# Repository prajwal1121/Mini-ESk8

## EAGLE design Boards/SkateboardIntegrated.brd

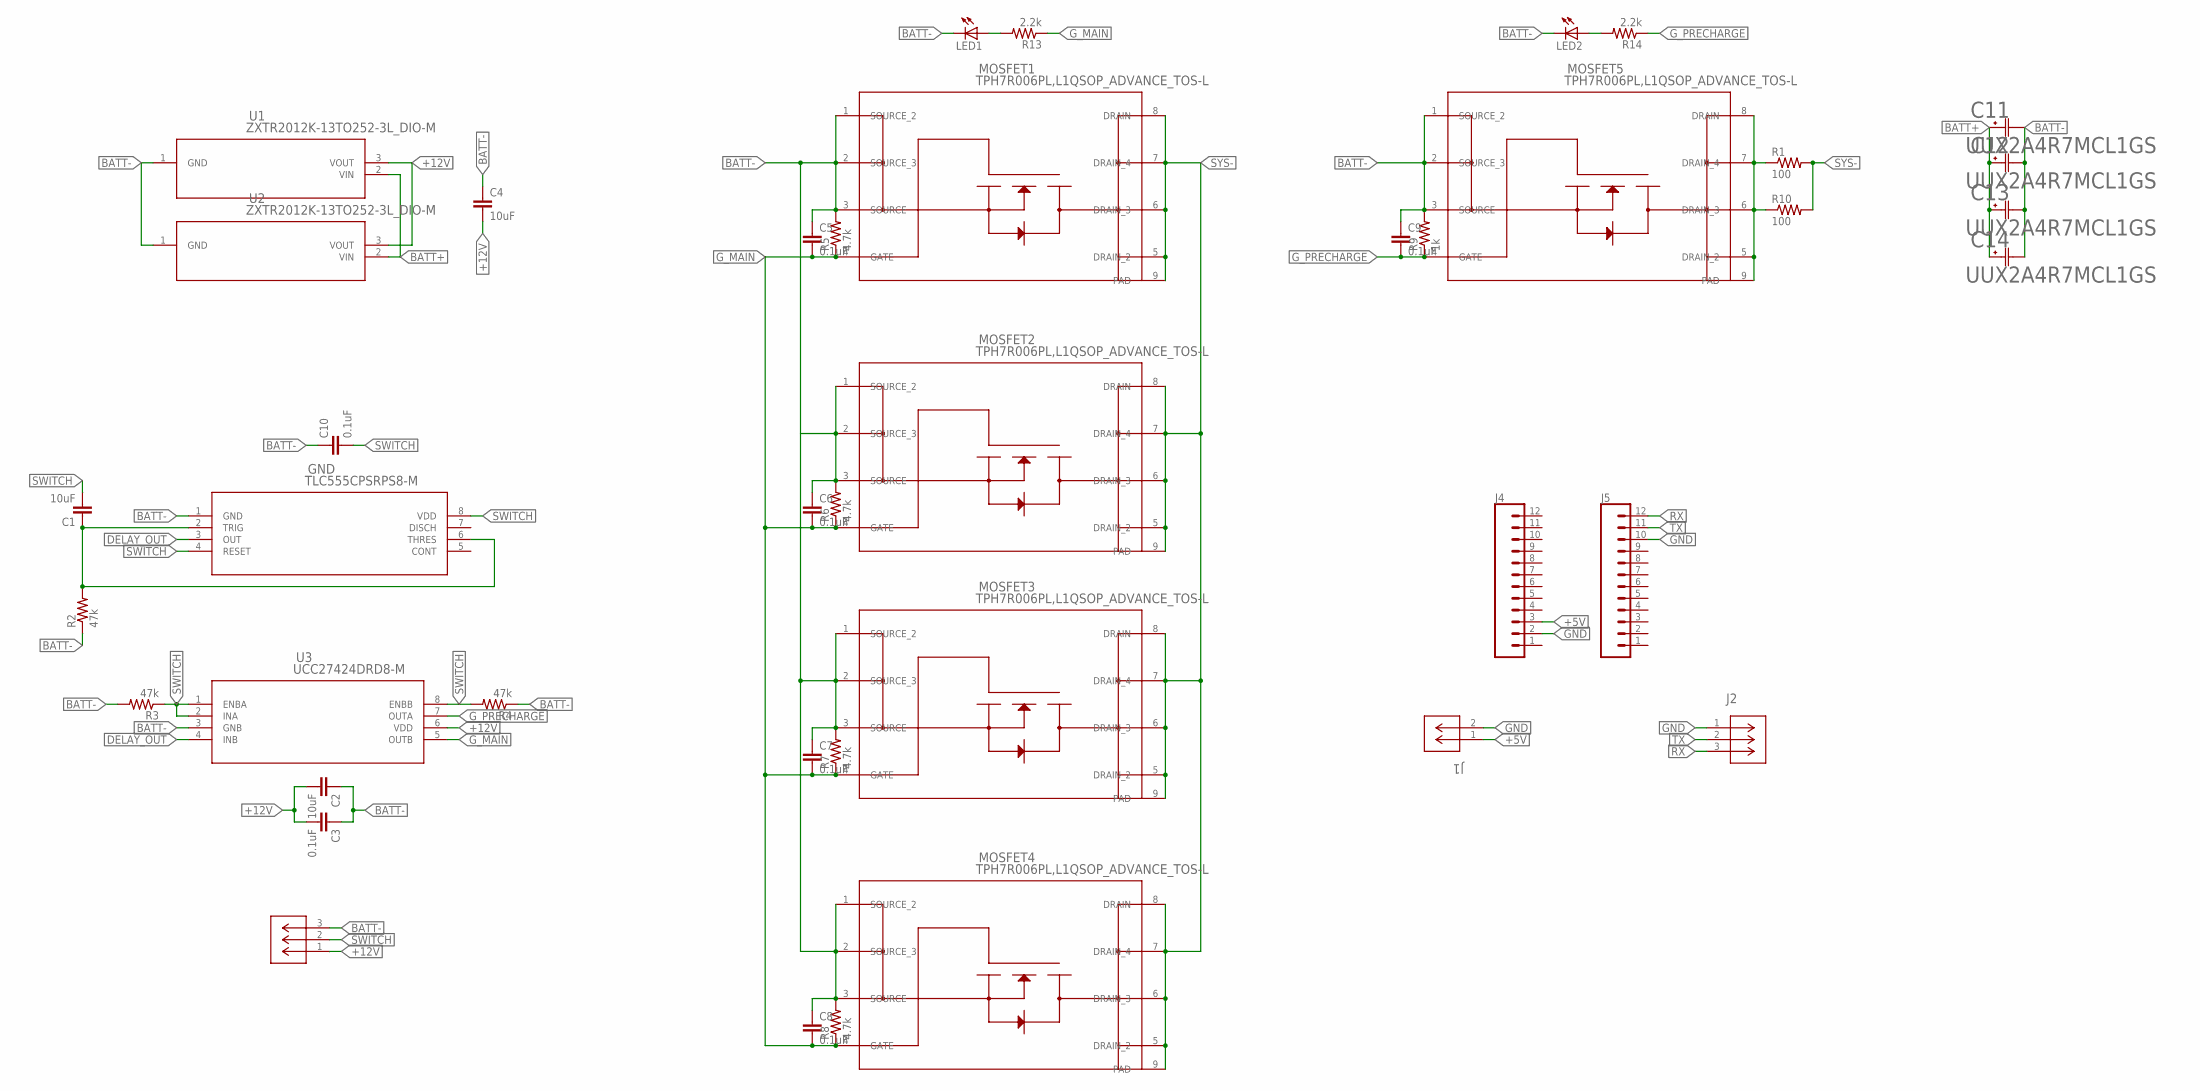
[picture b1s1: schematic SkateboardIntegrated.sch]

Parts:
C1, C2, C4: 10uF; 0805
C3, C5, C6, C7, C8, C9, C10: 0.1uF; 0805
C11, C12, C13, C14: UUX2A4R7MCL1GS; CAP_UCD_8X6P2_NCH
GND: TLC555CPSRPS8-M; PS8-M
J1: 1775470-2; CONN2_1775470-2_TEC
J2, J3: 1775470-3; CONN3_1775470-3_TEC
J4, J5: CONN_12SMD_ALT; 1X12_SMD_ALT
LED1, LED2: LEDCHIPLED_0805; CHIPLED_0805
MOSFET1, MOSFET2, MOSFET3, MOSFET4, MOSFET5: TPH7R006PL,L1QSOP_ADVANCE_TOS-L; SOP_ADVANCE_TOS-L
R1, R10: 100; R2512
R2, R3, R4: 47k; R0805
R5, R6, R7, R8: 4.7k; R0805
R9: 1k; R0805
R13, R14: 2.2k; R0805
U1, U2: ZXTR2012K-13TO252-3L_DIO-M; TO252-3L_DIO-M
U3: UCC27424DRD8-M; D8-M

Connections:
+5V: J1.1, J4.3
+12V: C2.2, C3.2, C4.2, J3.1, U1.3 (VOUT), U2.3 (VOUT), U3.6 (VDD)
BATT+: C11.1, C12.1, C13.1, C14.1, U1.2 (VIN), U2.2 (VIN)
BATT-: C2.1, C3.1, C4.1, C5.1, C6.1, C7.1, C8.1, C9.1, C10.1, C11.2, C12.2, C13.2, C14.2, GND.1 (GND), J3.3, LED1.C, LED2.C, MOSFET1.1 (SOURCE_2), MOSFET1.2 (SOURCE_3), MOSFET1.3 (SOURCE), MOSFET2.1 (SOURCE_2), MOSFET2.2 (SOURCE_3), MOSFET2.3 (SOURCE), MOSFET3.1 (SOURCE_2), MOSFET3.2 (SOURCE_3), MOSFET3.3 (SOURCE), MOSFET4.1 (SOURCE_2), MOSFET4.2 (SOURCE_3), MOSFET4.3 (SOURCE), MOSFET5.1 (SOURCE_2), MOSFET5.2 (SOURCE_3), MOSFET5.3 (SOURCE), R2.1, R3.2, R4.1, R5.2, R6.2, R7.2, R8.2, R9.2, U1.1 (GND), U2.1 (GND), U3.3 (GNB)
DELAY_OUT: GND.3 (OUT), U3.4 (INB)
GND: J1.2, J2.1, J4.2, J5.10
G_MAIN: C5.2, C6.2, C7.2, C8.2, MOSFET1.4 (GATE), MOSFET2.4 (GATE), MOSFET3.4 (GATE), MOSFET4.4 (GATE), R5.1, R6.1, R7.1, R8.1, R13.1, U3.5 (OUTB)
G_PRECHARGE: C9.2, MOSFET5.4 (GATE), R9.1, R14.1, U3.7 (OUTA)
unnamed: C1.1, GND.2 (TRIG), GND.6 (THRES), R2.2
unnamed: MOSFET5.5 (DRAIN_2), MOSFET5.6 (DRAIN_3), MOSFET5.7 (DRAIN_4), MOSFET5.8 (DRAIN), MOSFET5.9 (PAD), R1.1, R10.1
unnamed: LED1.A, R13.2
unnamed: LED2.A, R14.2
RX: J2.3, J5.12
SWITCH: C1.2, C10.2, GND.4 (RESET), GND.8 (VDD), J3.2, R3.1, R4.2, U3.1 (ENBA), U3.2 (INA), U3.8 (ENBB)
SYS-: MOSFET1.5 (DRAIN_2), MOSFET1.6 (DRAIN_3), MOSFET1.7 (DRAIN_4), MOSFET1.8 (DRAIN), MOSFET1.9 (PAD), MOSFET2.5 (DRAIN_2), MOSFET2.6 (DRAIN_3), MOSFET2.7 (DRAIN_4), MOSFET2.8 (DRAIN), MOSFET2.9 (PAD), MOSFET3.5 (DRAIN_2), MOSFET3.6 (DRAIN_3), MOSFET3.7 (DRAIN_4), MOSFET3.8 (DRAIN), MOSFET3.9 (PAD), MOSFET4.5 (DRAIN_2), MOSFET4.6 (DRAIN_3), MOSFET4.7 (DRAIN_4), MOSFET4.8 (DRAIN), MOSFET4.9 (PAD), R1.2, R10.2
TX: J2.2, J5.11

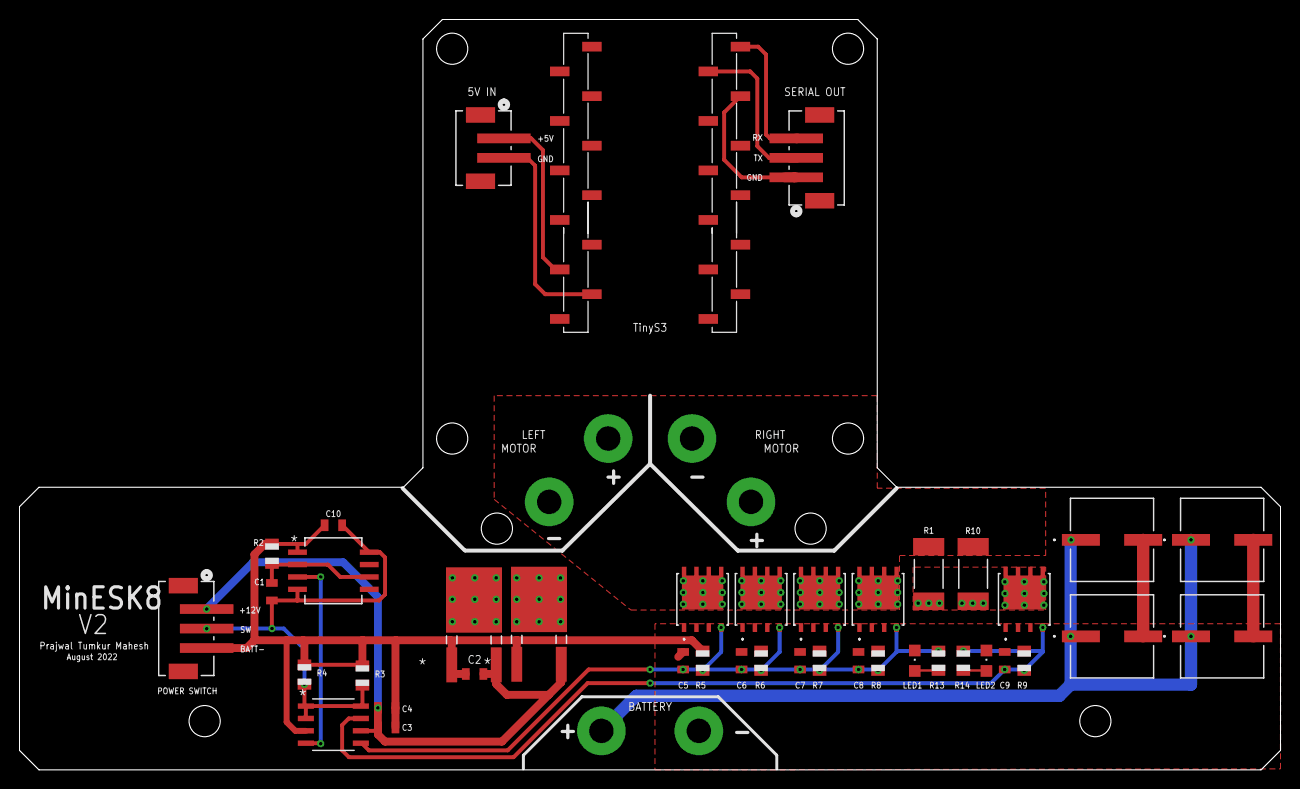
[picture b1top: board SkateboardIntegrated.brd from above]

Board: 2 copper layers, 129.4 x 77.0 mm, 42 parts (0 on the bottom side), 16 nets.

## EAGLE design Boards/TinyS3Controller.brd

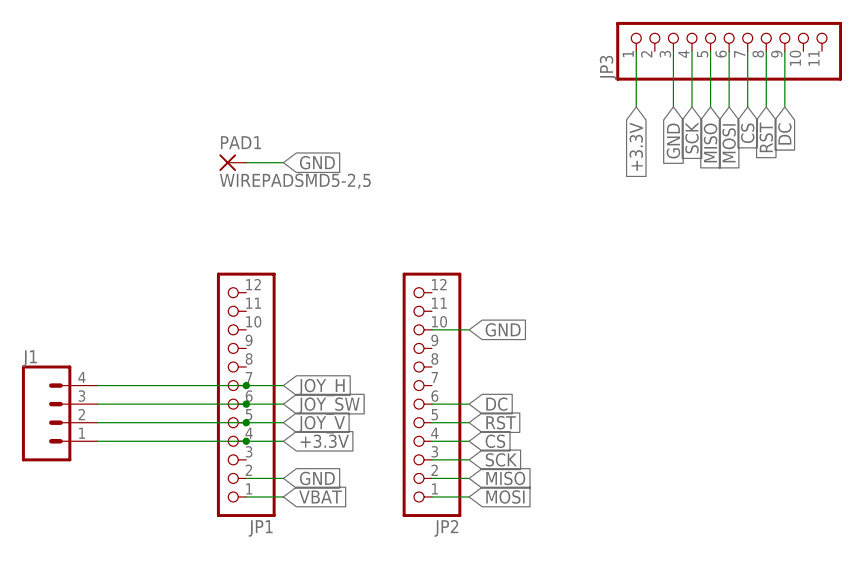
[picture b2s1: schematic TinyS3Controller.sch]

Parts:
J1: CONN_04PTH; 1X04
JP1, JP2: PINHD-1X12-CB; 1X12-CB
JP3: PINHD-1X11; 1X11
PAD1: WIREPADSMD5-2,5; 5-2,5

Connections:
+3.3V: J1.1, JP1.4, JP3.1
CS: JP2.4, JP3.7
DC: JP2.6, JP3.9
GND: JP1.2, JP2.10, JP3.3, PAD1.1
JOY_H: J1.4, JP1.7
JOY_SW: J1.3, JP1.6
JOY_V: J1.2, JP1.5
MISO: JP2.2, JP3.5
MOSI: JP2.1, JP3.6
RST: JP2.5, JP3.8
SCK: JP2.3, JP3.4
VBAT: JP1.1

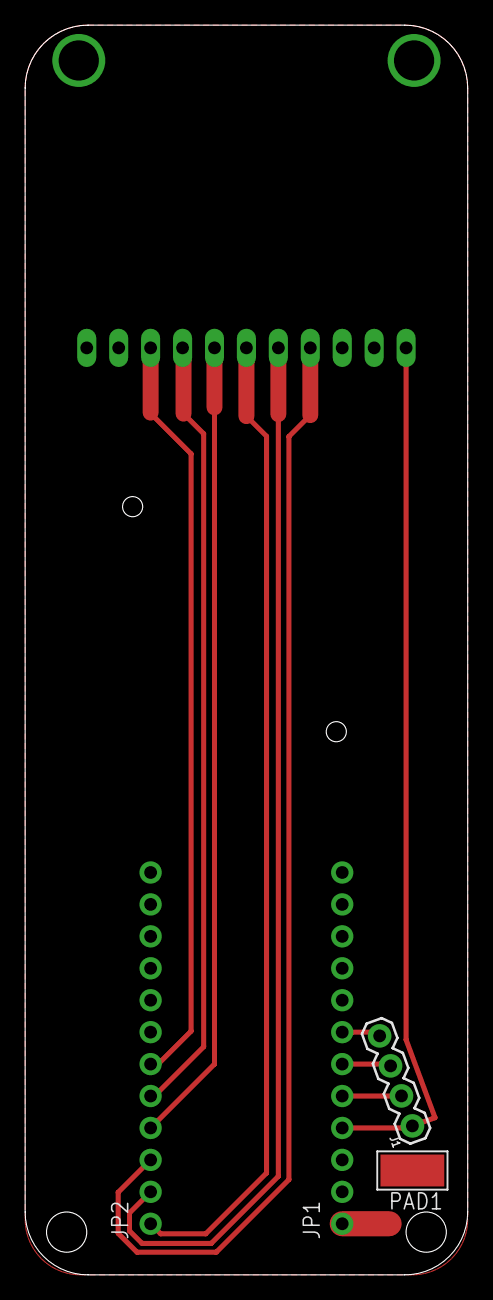
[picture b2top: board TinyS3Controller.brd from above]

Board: 2 copper layers, 35.2 x 99.4 mm, 5 parts (1 on the bottom side), 11 nets.

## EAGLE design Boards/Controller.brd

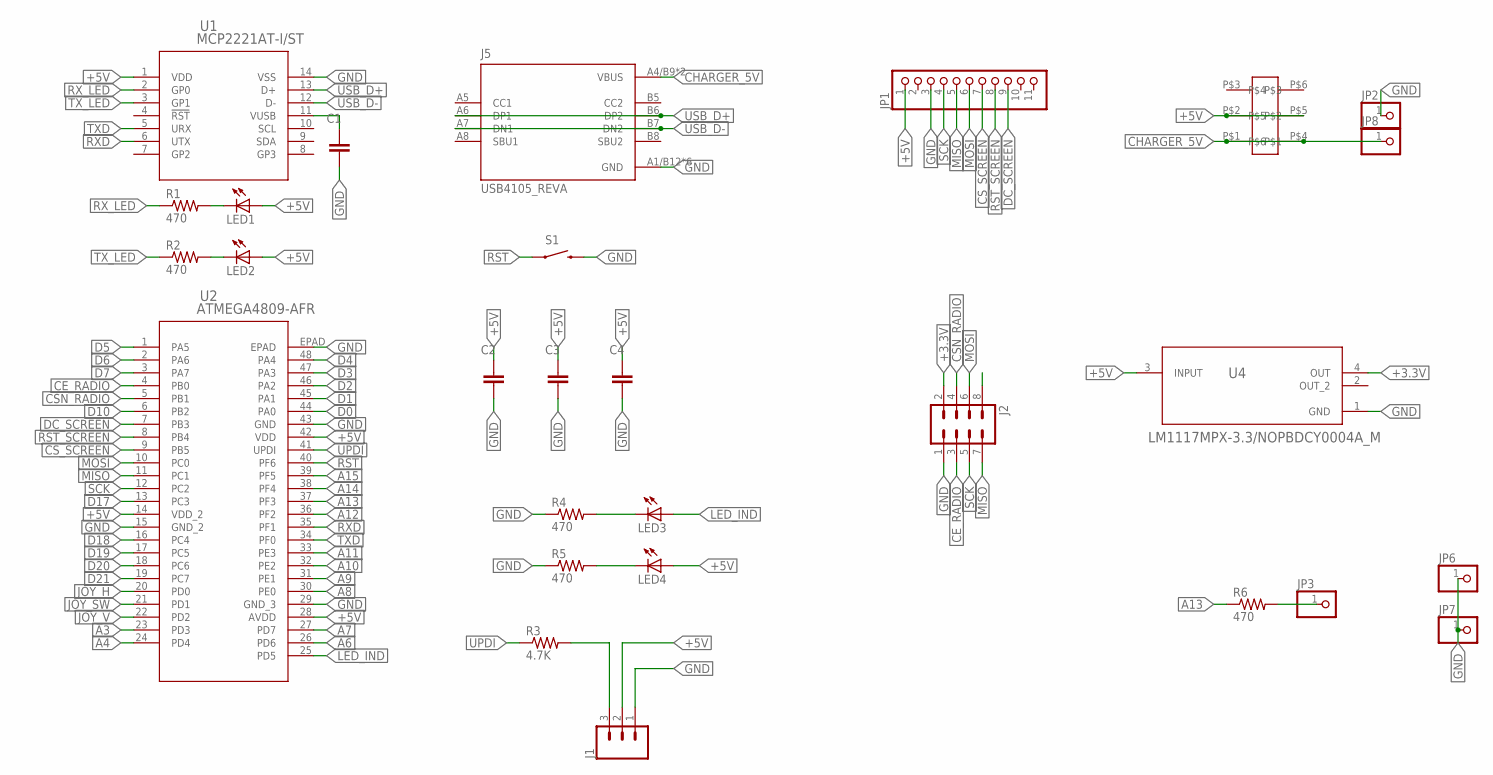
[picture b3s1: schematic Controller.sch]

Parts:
C1: 0.22uF; CAP_0805
C2, C3, C4: 0.1uF; CAP_0805
J1: CONN_03SMD_RA_MALE; 1X03_SMD_RA_MALE
J2: MA04-2
J5: USB4105_REVA; GCT_USB4105_REVA
JP1: PINHD-1X11; 1X11
JP2, JP3, JP6, JP7, JP8: PINHD-1X1; 1X01
LED1, LED2, LED3, LED4: LEDCHIPLED_0805; CHIPLED_0805
R1, R2, R4, R5, R6: 470; R0805
R3: 4.7K; R0805
S1: RS032G05A3SM-SPST-MOMENTARY-SWSMD-1101NE; TACTILE-SWITCH-1101NE
U1: MCP2221AT-I/ST; TSSOP14_ST_MCH
U2: ATMEGA4809-AFR; TQFP48_7X7MC_MCH
U4: LM1117MPX-3.3/NOPBDCY0004A_M; DCY0004A_M
U$47: JS202011JAQN

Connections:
+3.3V: J2.2, U4.4 (OUT)
+5V: C2.1, C3.1, C4.1, J1.2, JP1.1, LED1.A, LED2.A, LED4.A, U1.1 (VDD), U2.14 (VDD_2), U2.28 (AVDD), U2.42 (VDD), U4.3 (INPUT), U$47.P$2, U$47.P$5
A3: U2.23 (PD3)
A4: U2.24 (PD4)
A6: U2.26 (PD6)
A7: U2.27 (PD7)
A8: U2.30 (PE0)
A9: U2.31 (PE1)
A10: U2.32 (PE2)
A11: U2.33 (PE3)
A12: U2.36 (PF2)
A13: R6.1, U2.37 (PF3)
A14: U2.38 (PF4)
A15: U2.39 (PF5)
CE_RADIO: J2.3, U2.4 (PB0)
CHARGER_5V: J5.A4/B9 (VBUS), J5.B4/A9 (VBUS), JP8.1, U$47.P$1, U$47.P$4
CSN_RADIO: J2.4, U2.5 (PB1)
CS_SCREEN: JP1.7, U2.9 (PB5)
D0: U2.44 (PA0)
D1: U2.45 (PA1)
D2: U2.46 (PA2)
D3: U2.47 (PA3)
D4: U2.48 (PA4)
D5: U2.1 (PA5)
D6: U2.2 (PA6)
D7: U2.3 (PA7)
D10: U2.6 (PB2)
D17: U2.13 (PC3)
D18: U2.16 (PC4)
D19: U2.17 (PC5)
D20: U2.18 (PC6)
D21: U2.19 (PC7)
DC_SCREEN: JP1.9, U2.7 (PB3)
GND: C1.2, C2.2, C3.2, C4.2, J1.1, J2.1, J5.A1/B12 (GND), J5.B1/A12 (GND), J5.G1 (GND), J5.G2 (GND), J5.G3 (GND), J5.G4 (GND), JP1.3, JP2.1, JP6.1, JP7.1, R4.1, R5.1, S1.2, U1.14 (VSS), U2.15 (GND_2), U2.29 (GND_3), U2.43 (GND), U2.EPAD, U4.1 (GND)
JOY_H: U2.20 (PD0)
JOY_SW: U2.21 (PD1)
JOY_V: U2.22 (PD2)
LED_IND: LED3.A, U2.25 (PD5)
MISO: J2.7, JP1.5, U2.11 (PC1)
MOSI: J2.6, JP1.6, U2.10 (PC0)
unnamed: LED1.C, R1.2
unnamed: LED2.C, R2.2
unnamed: C1.1, U1.11 (VUSB)
unnamed: JP3.1, R6.2
unnamed: LED3.C, R4.2
unnamed: LED4.C, R5.2
unnamed: J1.3, R3.2
OUT_2: U4.2 (OUT_2)
RST: S1.1, U2.40 (PF6)
RST_SCREEN: JP1.8, U2.8 (PB4)
RXD: U1.6 (UTX), U2.35 (PF1)
RX_LED: R1.1, U1.2 (GP0)
SCK: J2.5, JP1.4, U2.12 (PC2)
TXD: U1.5 (URX), U2.34 (PF0)
TX_LED: R2.1, U1.3 (GP1)
UPDI: R3.1, U2.41 (UPDI)
USB_D+: J5.A6 (DP1), J5.B6 (DP2), U1.13 (D+)
USB_D-: J5.A7 (DN1), J5.B7 (DN2), U1.12 (D-)

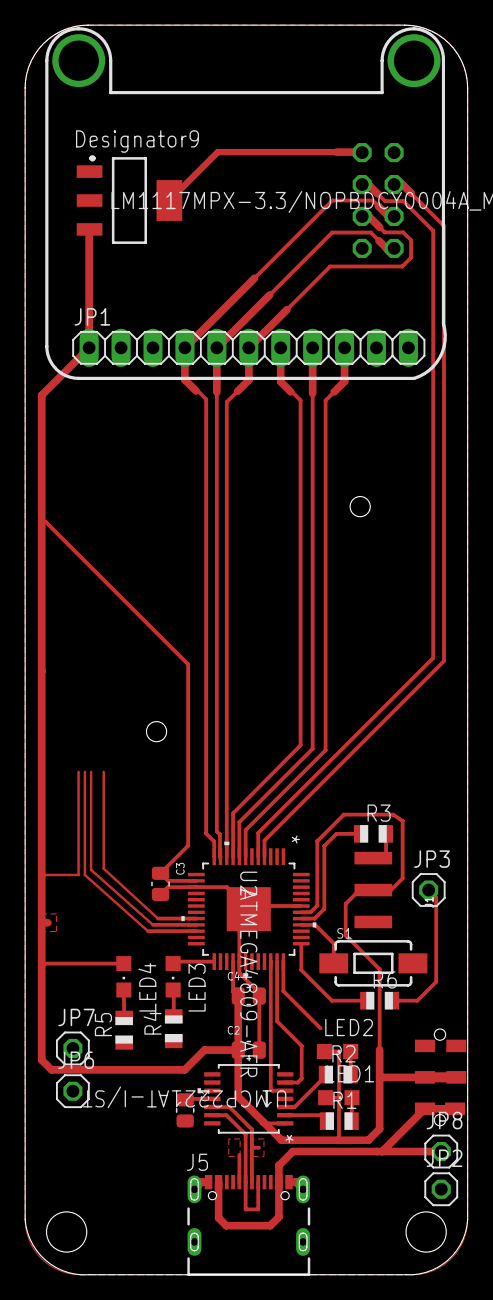
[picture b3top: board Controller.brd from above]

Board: 2 copper layers, 35.2 x 99.4 mm, 28 parts (1 on the bottom side), 29 nets.

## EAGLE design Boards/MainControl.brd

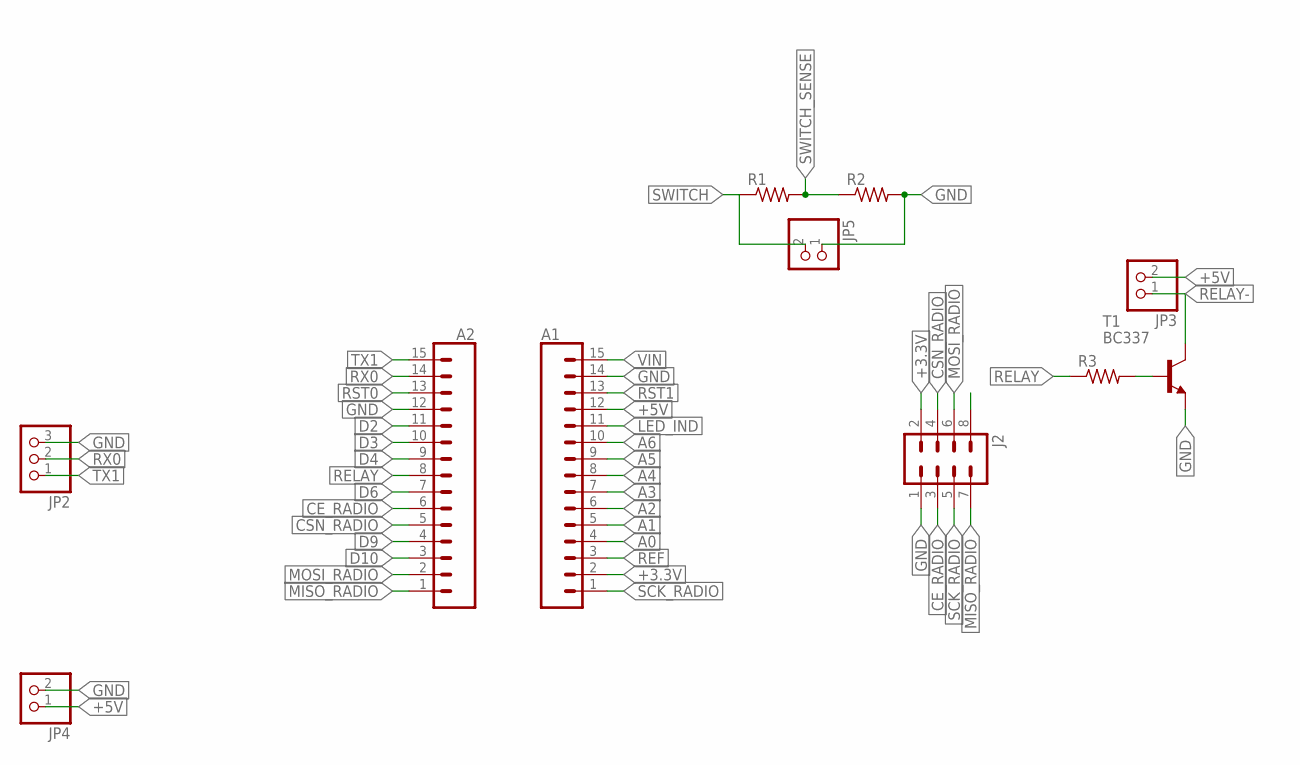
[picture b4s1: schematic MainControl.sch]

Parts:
A1, A2: CONN_15; 1X15
J2: MA04-2
JP2: PINHD-1X3; 1X03
JP3, JP4, JP5: PINHD-1X2; 1X02
R1, R2, R3: R-US_0204/7; 0204/7
T1: BC337; TO92

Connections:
+3.3V: A1.2, J2.2
+5V: A1.12, JP3.2, JP4.1
A0: A1.4
A1: A1.5
A2: A1.6
A3: A1.7
A4: A1.8
A5: A1.9
A6: A1.10
CE_RADIO: A2.6, J2.3
CSN_RADIO: A2.5, J2.4
D2: A2.11
D3: A2.10
D4: A2.9
D6: A2.7
D9: A2.4
D10: A2.3
GND: A1.14, A2.12, J2.1, JP2.3, JP4.2, JP5.1, R2.2, T1.1 (E)
LED_IND: A1.11
MISO_RADIO: A2.1, J2.7
MOSI_RADIO: A2.2, J2.6
unnamed: R3.2, T1.2 (B)
REF: A1.3
RELAY: A2.8, R3.1
RELAY-: JP3.1, T1.3 (C)
RST0: A2.13
RST1: A1.13
RX0: A2.14, JP2.2
SCK_RADIO: A1.1, J2.5
SWITCH: JP5.2, R1.1
SWITCH_SENSE: R1.2, R2.1
TX1: A2.15, JP2.1
VIN: A1.15

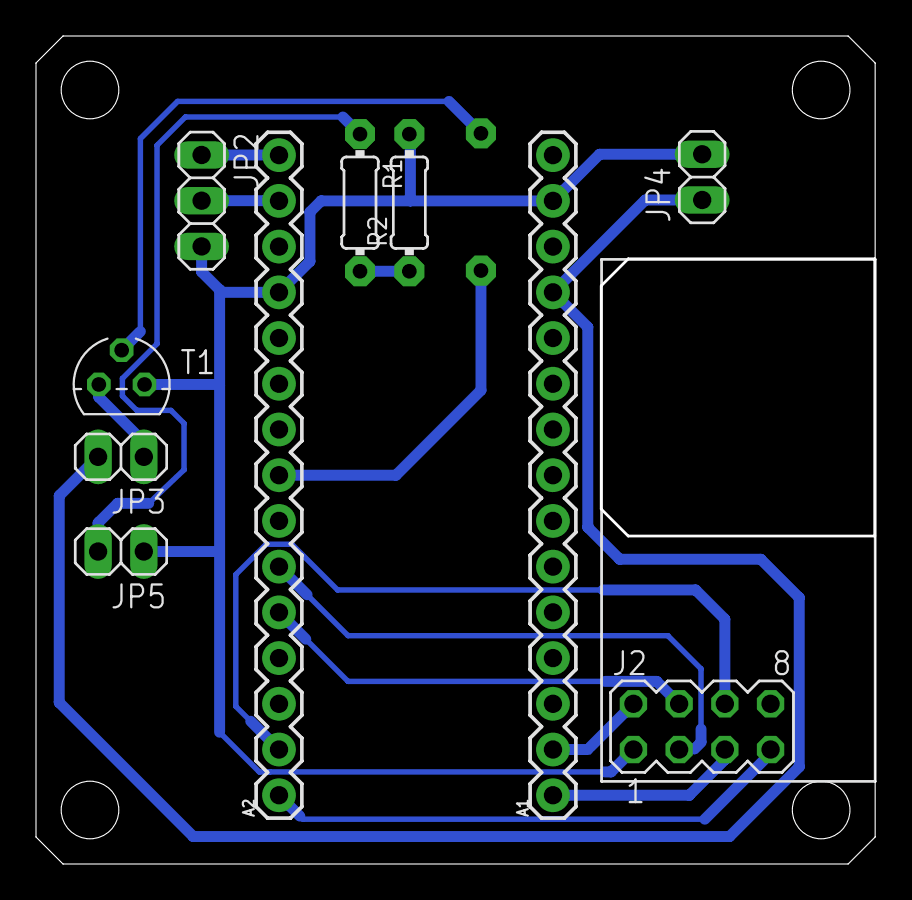
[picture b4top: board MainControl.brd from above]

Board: 2 copper layers, 46.5 x 45.8 mm, 11 parts (1 on the bottom side), 15 nets.

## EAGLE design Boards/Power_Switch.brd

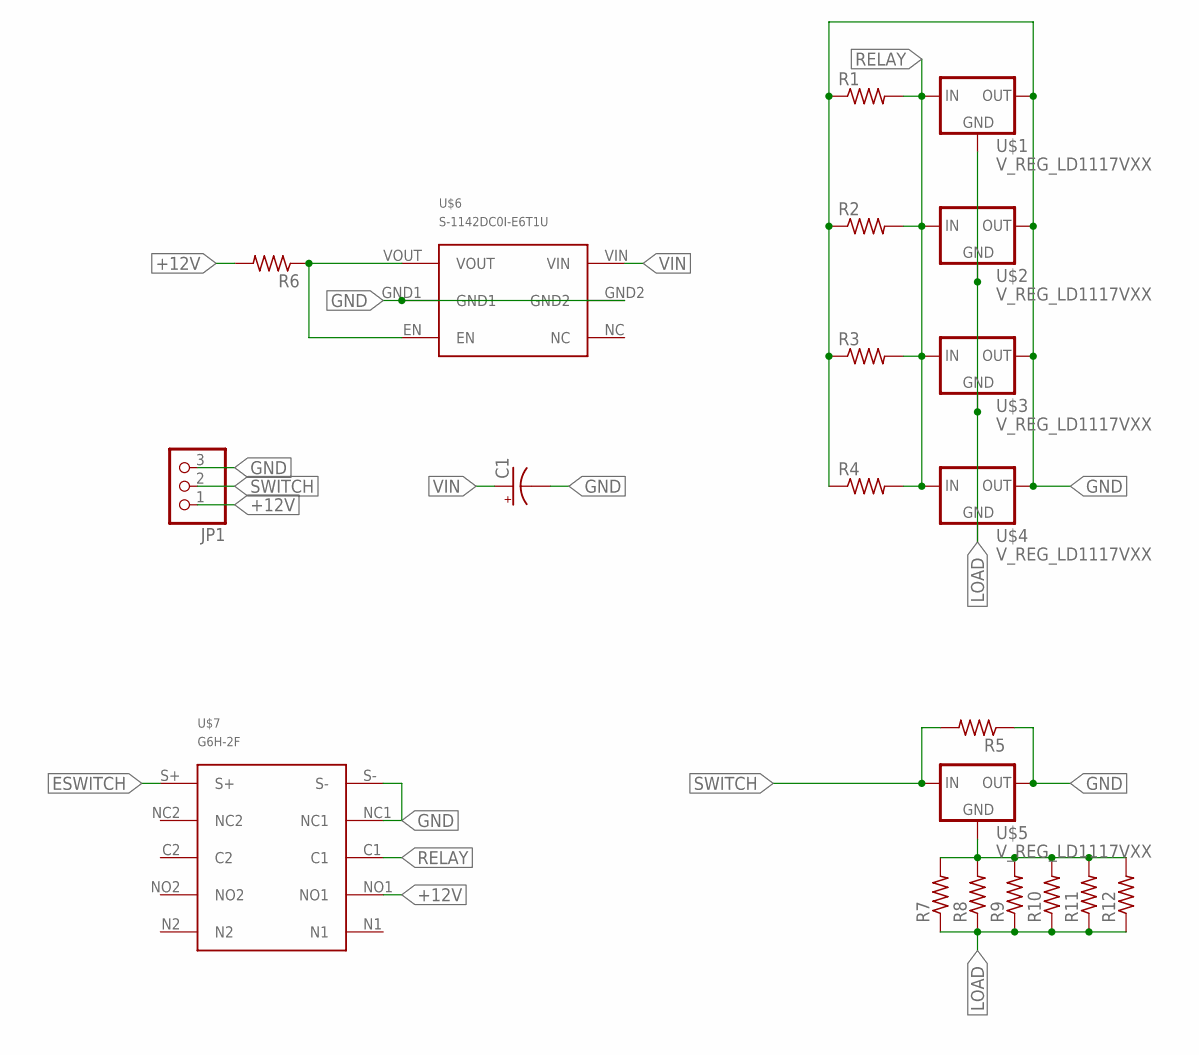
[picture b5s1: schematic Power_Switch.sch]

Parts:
C1: CPOL-US153CLV-0810; 153CLV-0810
JP1: PINHD-1X3; 1X03
R1, R2, R3, R4, R5, R6, R7, R8, R9, R10, R11, R12: R-US_R0805; R0805
U$1, U$2, U$3, U$4, U$5: V_REG_LD1117VXX; 78XXL
U$6: S-1142DC0I-E6T1U
U$7: G6H-2F

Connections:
+12V: JP1.1, R6.2, U$7.NO1
ESWITCH: U$7.S+
GND: C1.-, JP1.3, R1.1, R2.1, R3.1, R4.1, R5.1, U$1.OUT, U$2.OUT, U$3.OUT, U$4.OUT, U$5.OUT, U$6.GND1, U$6.GND2, U$7.NC1, U$7.S-
LOAD: R7.1, R8.1, R9.1, R10.1, R11.1, R12.1, U$1.GND, U$2.GND, U$3.GND, U$4.GND
unnamed: R6.1, U$6.EN, U$6.VOUT
unnamed: R7.2, R8.2, R9.2, R10.2, R11.2, R12.2, U$5.GND
RELAY: R1.2, R2.2, R3.2, R4.2, U$1.IN, U$2.IN, U$3.IN, U$4.IN, U$7.C1
SWITCH: JP1.2, R5.2, U$5.IN
VIN: C1.+, U$6.VIN

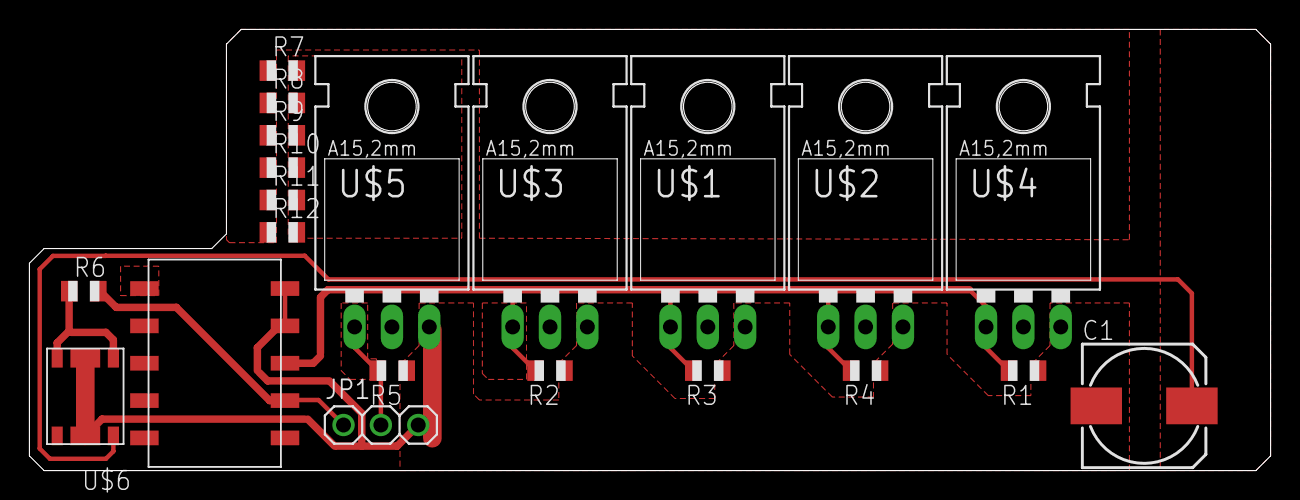
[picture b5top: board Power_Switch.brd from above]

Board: 2 copper layers, 84.4 x 30.0 mm, 21 parts (0 on the bottom side), 8 nets.

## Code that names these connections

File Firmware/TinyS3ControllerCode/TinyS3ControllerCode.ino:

#include <UMS3.h>
UMS3 ums3;

#include <esp_now.h>
#include <WiFi.h>

//#define USE_ASYNC_UPDATES

#include <Adafruit_GFX.h>
#include <Adafruit_ST7789.h> // Hardware-specific library for ST7789
#include <SPI.h>

//SCREEN PINS
#define SCREEN_CS   34
#define SCREEN_RST  9 
#define SCREEN_DC   8
//Create TFT object with correct pins
Adafruit_ST7789 tft = Adafruit_ST7789(SCREEN_CS, SCREEN_DC, SCREEN_RST);

uint16_t boxColor = 0x76D8;
uint16_t axisColor = 0x2207;

//JOYSTICK PINS
#define JOY_V  A0
#define JOY_H  A2 
#define JOY_SW A1
int joystick_x = 128;
int joystick_y = 128;
bool joystick_sw = 0;
int lastPosX = 0;
int lastPosY = 0;

//BATTERY PINS
float remoteBatteryVoltage = 0.0;
float lastRemoteBatteryVoltage = 0.0;
float remoteBatteryVoltageOffset = 0.0;

//BOARD BATTERY
byte boardBatteryCells = 10;
float boardBatteryVoltage = 0.0;
float lastBoardBatteryVoltage = 0.0;
float boardBatteryVoltageOffset = 0.0;

//BOARD ODOMETRY
int8_t mph = 0;
int8_t lastMph = 0;
int totalMiles = 69;
int tripMiles = 240;
const float rpmScaling = ((((90.0/25.4)/12.0)/5280.0)*3.14)*60.0;
const float motorPolePairs = 10.0;

//RADIO SETUP
//A: F4:12:FA:4F:A5:B0
uint8_t broadcastAddress[] = {0xF4, 0x12, 0xFA, 0x4F, 0xA5, 0xB0};

//Struct for holding board telemetry
typedef struct TelemetryStruct {
  float voltage;
  long rpm;
  long tach_abs;
} TelemetryStruct;

TelemetryStruct telemetry;
esp_now_peer_info_t peerInfo;

// Callback when data is sent
void OnDataSent(const uint8_t *mac_addr, esp_now_send_status_t status) {
//  Serial.print("\r\nLast Packet Send Status:\t");
//  Serial.println(status == ESP_NOW_SEND_SUCCESS ? "Delivery Success" : "Delivery Fail");
//  if (status ==0){
//    success = "Delivery Success :)";
//  }
//  else{
//    success = "Delivery Fail :(";
//  }
}

// Callback when data is received
void OnDataRecv(const uint8_t * mac, const uint8_t *incomingData, int len) {
  memcpy(&telemetry, incomingData, sizeof(telemetry));
  boardBatteryVoltage = telemetry.voltage;
  mph = telemetry.rpm/motorPolePairs*rpmScaling;
  tripMiles = telemetry.tach_abs;
}

void boardBatteryDisplay(){
  if (abs(boardBatteryVoltage-lastBoardBatteryVoltage)>0.1){
    tft.fillRoundRect(1, 0, tft.width()-2, 4, 2, ST77XX_BLACK);
    tft.drawRoundRect(1, 0, tft.width()-2, 4, 2, ST77XX_GREEN);
    
    int fillamount = boardBatteryVoltage/(4.2*boardBatteryCells)*(tft.width()-2);
    uint16_t color = 0;
    if (boardBatteryVoltage > (3.8*boardBatteryCells) and boardBatteryVoltage <= (4.2*boardBatteryCells)){
      color = ST77XX_GREEN;
    }
    else if (boardBatteryVoltage > (3.4*boardBatteryCells) and boardBatteryVoltage <= (3.8*boardBatteryCells)){
      color = ST77XX_YELLOW;
    }
    else if (boardBatteryVoltage <= (3.4*boardBatteryCells)){
      color = ST77XX_RED;
    }
    tft.fillRoundRect(1, 0, fillamount, 4, 2, color); 
  
    lastBoardBatteryVoltage = boardBatteryVoltage;
  }
}

void remoteBatteryDisplay(){
  remoteBatteryVoltage = ums3.getBatteryVoltage()+remoteBatteryVoltageOffset;
  
  if (abs(remoteBatteryVoltage-lastRemoteBatteryVoltage)>0.1){
    tft.fillRoundRect(tft.width()/3, 6, tft.width()/3, 4, 2, ST77XX_BLACK);
    tft.drawRoundRect(tft.width()/3, 6, tft.width()/3, 4, 2, ST77XX_GREEN);
    
    int fillamount = remoteBatteryVoltage/4.2*(tft.width()/3);
    uint16_t color = 0;
    if (remoteBatteryVoltage > 3.8 and remoteBatteryVoltage <= 4.2){
      color = ST77XX_GREEN;
    }
    else if (remoteBatteryVoltage > 3.4 and remoteBatteryVoltage <= 3.8){
      color = ST77XX_YELLOW;
    }
    else if (remoteBatteryVoltage <= 3.4){
      color = ST77XX_RED;
    }
    tft.fillRoundRect(tft.width()/3, 6, fillamount, 4, 2, color); 
  
    lastRemoteBatteryVoltage = remoteBatteryVoltage;
  }
}

void joystickDisplay(){
  tft.drawRoundRect(tft.width()/2+2, tft.height()/3-25, tft.width()/2-2, tft.height()/1.8, 5, boxColor);
  tft.drawFastVLine(3*tft.width()/4, tft.height()/3-25, tft.height()/1.8, axisColor);
  tft.drawFastHLine(tft.width()/2+2, (tft.height()/3-25) + (tft.height()/1.8)/2, tft.width()/2-2, axisColor);

  int centerY = (tft.height()/3-25) + (tft.height()/1.8)/2;
  int centerX = 3*tft.width()/4;
  int pos_x = map(joystick_x,0,255,centerX-(tft.width()/2)/2+8,centerX+(tft.width()/2-2)/2-8);
  int pos_y = map(joystick_y,0,255,centerY+(tft.height()/1.8)/2-8,centerY-(tft.height()/1.8)/2+8);

  if ((pos_x != lastPosX) or (pos_y!= lastPosY)){
    tft.fillCircle(lastPosX,lastPosY,5,ST77XX_BLACK);
    lastPosX = pos_x;
    lastPosY = pos_y;
  }
  tft.fillCircle(pos_x,pos_y,5,ST77XX_RED);
}

void readInputs(){
  joystick_x = map(analogRead(JOY_H),660,3220,0,255);
  if(joystick_x >= 255){
    joystick_x = 255;
  }
  if(joystick_x <= 0){
    joystick_x = 0;
  } 
  
  joystick_y = map(analogRead(JOY_V),630,3220 ,255, 0);
  if(joystick_y >= 255){
    joystick_y = 255;
  }
  if(joystick_y <= 0){
    joystick_y = 0;
  } 

  joystick_sw = digitalRead(JOY_SW);
}

void odometryDisplay(){
  byte speedLocation;
  tft.setTextSize(8);
  
  if (lastMph != mph){
    if (lastMph > 9 or lastMph < 0){
      speedLocation = tft.width()/5-35;
    }
    else{
      speedLocation = tft.width()/5-10;
    }
    tft.setCursor(speedLocation, tft.height()/3-25);
    tft.setTextColor(ST77XX_BLACK);
    tft.print(lastMph);
    lastMph = mph;
  }
  
  if (mph > 9 or mph < 0){
    speedLocation = tft.width()/5-35;
  }
  else{
    speedLocation = tft.width()/5-10;
  }
  tft.setCursor(speedLocation, tft.height()/3-25);
  tft.setTextColor(ST77XX_WHITE);
  tft.print(mph);

  tft.setTextSize(2);
  tft.setCursor(tft.width()/5-7, 4*tft.height()/5-27);
  tft.print("MPH");
  
  tft.drawRoundRect(2, 3*tft.height()/4, tft.width()/2-2, tft.height()/4, 5, boxColor);
  tft.drawRoundRect(tft.width()/2+2, 3*tft.height()/4, tft.width()/2-2, tft.height()/4, 5, boxColor);

  tft.setTextSize(0);
  tft.setCursor(tft.width()/4-15, 3*tft.height()/4+3);
  tft.print("TOTAL");
  tft.setTextSize(1);
  tft.setCursor(tft.width()/4-15, 3*tft.height()/4+20);
  tft.print(totalMiles);

  tft.setTextSize(0);
  tft.setCursor(3*tft.width()/4-11, 3*tft.height()/4+3);
  tft.print("TRIP");
  tft.setTextSize(1);
  tft.setCursor(3*tft.width()/4-11, 3*tft.height()/4+20);
  tft.print(tripMiles);
}


void setup() {
  //Initialize all board peripherals
  ums3.begin();

  //Confugure Peer Communication
  //Set device as a Wi-Fi Station
  WiFi.mode(WIFI_STA);

  //Init ESP-NOW
  if (esp_now_init() != ESP_OK) {
    return;
  }

  //Once ESPNow is successfully Init, we will register for Send CB to
  // get the status of Trasnmitted packet
  esp_now_register_send_cb(OnDataSent);
  
  // Register peer
  memcpy(peerInfo.peer_addr, broadcastAddress, 6);
  peerInfo.channel = 0;  
  peerInfo.encrypt = false;
  
  // Add peer        
  if (esp_now_add_peer(&peerInfo) != ESP_OK){
    return;
  }
  
  // Register for a callback function that will be called when data is received
  esp_now_register_recv_cb(OnDataRecv);

  Serial.begin(115200);
  
  //Configure Joystick Pins
  pinMode(JOY_V,INPUT);
  pinMode(JOY_H,INPUT);
  pinMode(JOY_SW,INPUT);

  //Initialize screen and set to black
  tft.init(135, 240);
  tft.setRotation(3);
  tft.fillScreen(ST77XX_BLACK);
  joystickDisplay();
  odometryDisplay();
}

long lastbatterytime = millis();
long lastanimatetime = millis();
long lastinputtime = millis();
long lastodomtime = millis();
void loop() {
  if (millis()-lastinputtime > 10){
    readInputs();
    Serial.println(joystick_y);
    lastinputtime = millis();
  }
  if (millis()-lastanimatetime > 25){
    joystickDisplay();
    lastanimatetime = millis();
  }
  if (millis()-lastbatterytime > 1000){
    boardBatteryDisplay();
    remoteBatteryDisplay();
    lastbatterytime = millis();
  }
  if (millis()-lastodomtime > 250){
    odometryDisplay();
    lastodomtime = millis();
  }

  byte outputValue =  joystick_y;
  esp_err_t result = esp_now_send(broadcastAddress, (uint8_t *) &outputValue, sizeof(outputValue));
  
//  radio.stopListening();
//  byte outputValue =  joystick_y;
//  radio.write(&outputValue, sizeof(outputValue));
//  
//  uint8_t pipe;
//  if (radio.available(&pipe)) {
//    TelemetryStruct received;
//    radio.read(&received, sizeof(received));
//    boardBatteryVoltage = received.voltage;
//    mph = received.rpm/motorPolePairs*rpmScaling;
//    tripMiles = received.tach_abs;
////    Serial2.print(F(" Recieved ")); 
////    Serial2.print(radio.getDynamicPayloadSize());
////    Serial2.print(F(" bytes on pipe "));
////    Serial2.print(pipe);
////    Serial2.print(F(": "));
////    Serial2.println(received.rpm );
//  }   
}

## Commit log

2022-09-06 Added TinyS3 Revision
2022-09-06 TinyS3 controller firmware upload
2022-09-06 TinyS3 PCB upload

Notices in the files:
parts and their libraries:
SparkFun-Connectors: Licensing: Creative Commons ShareAlike 4.0 International - https://creativecommons.org/licenses/by-sa/4.0
COPYRIGHT: Copyright (C) 2018 Accelerated Designs. All rights reserved
COPYRIGHT: Copyright (C) 2022 Ultra Librarian. All rights reserved.
